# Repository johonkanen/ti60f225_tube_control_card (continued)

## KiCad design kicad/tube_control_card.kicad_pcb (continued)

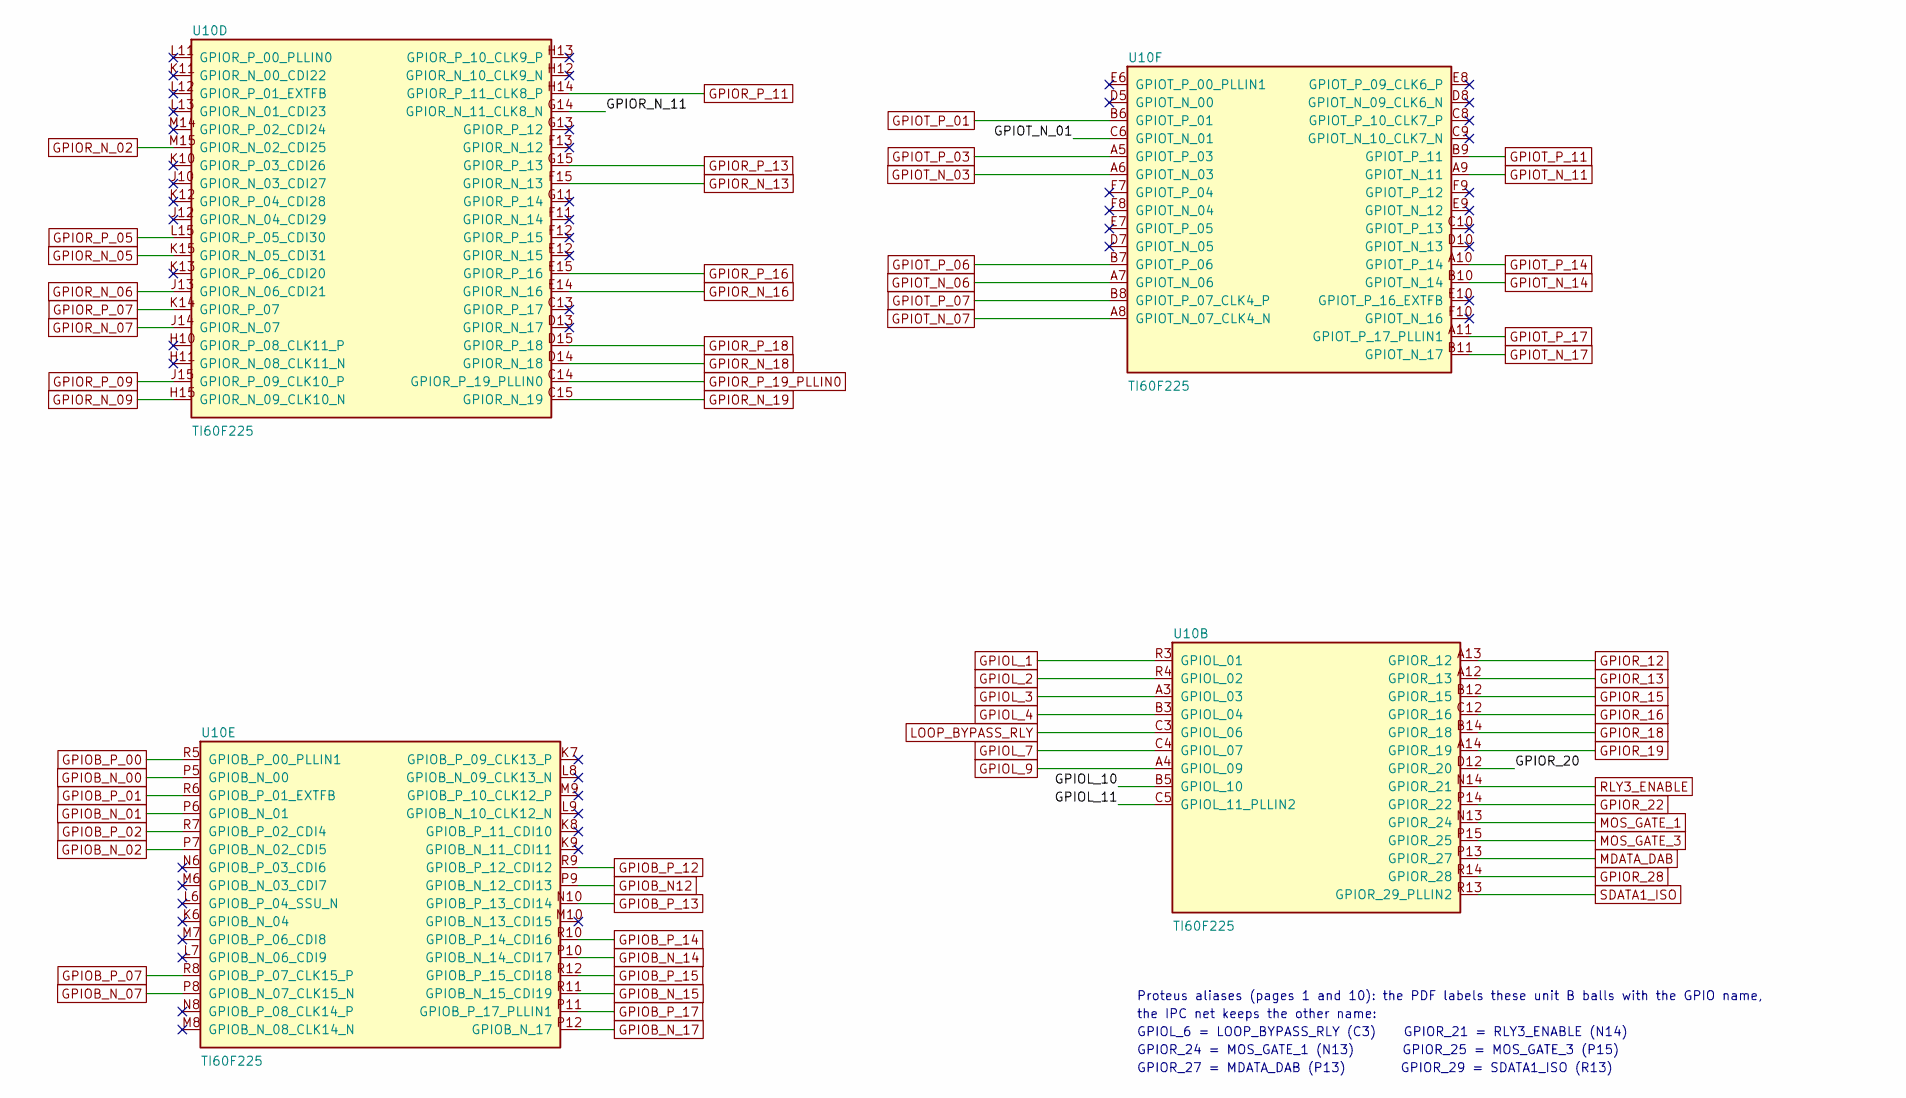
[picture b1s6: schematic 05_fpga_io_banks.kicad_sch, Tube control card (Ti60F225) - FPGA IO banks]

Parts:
U10: TI60F225; TFBGA-225_10x10mm_Layout15x15_P0.65mm

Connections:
/05 FPGA IO banks/GPIOL_10: U10.B5 (GPIOL_10); also elsewhere on the board
/05 FPGA IO banks/GPIOL_11: U10.C5 (GPIOL_11_PLLIN2); also elsewhere on the board
/05 FPGA IO banks/GPIOR_20: U10.D12 (GPIOR_20)
/05 FPGA IO banks/GPIOR_N_11: U10.G14 (GPIOR_N_11_CLK8_N)
/05 FPGA IO banks/GPIOT_N_01: U10.C6 (GPIOT_N_01)
GPIOB_N12: U10.P9 (GPIOB_N_12_CDI13); also elsewhere on the board
GPIOB_N_00: U10.P5 (GPIOB_N_00); also elsewhere on the board
GPIOB_N_01: U10.P6 (GPIOB_N_01); also elsewhere on the board
GPIOB_N_02: U10.P7 (GPIOB_N_02_CDI5); also elsewhere on the board
GPIOB_N_07: U10.P8 (GPIOB_N_07_CLK15_N); also elsewhere on the board
GPIOB_N_14: U10.P10 (GPIOB_N_14_CDI17); also elsewhere on the board
GPIOB_N_15: U10.R11 (GPIOB_N_15_CDI19); also elsewhere on the board
GPIOB_N_17: U10.P12 (GPIOB_N_17); also elsewhere on the board
GPIOB_P_00: U10.R5 (GPIOB_P_00_PLLIN1); also elsewhere on the board
GPIOB_P_01: U10.R6 (GPIOB_P_01_EXTFB); also elsewhere on the board
GPIOB_P_02: U10.R7 (GPIOB_P_02_CDI4); also elsewhere on the board
GPIOB_P_07: U10.R8 (GPIOB_P_07_CLK15_P); also elsewhere on the board
GPIOB_P_12: U10.R9 (GPIOB_P_12_CDI12); also elsewhere on the board
GPIOB_P_13: U10.N10 (GPIOB_P_13_CDI14); also elsewhere on the board
GPIOB_P_14: U10.R10 (GPIOB_P_14_CDI16); also elsewhere on the board
GPIOB_P_15: U10.R12 (GPIOB_P_15_CDI18); also elsewhere on the board
GPIOB_P_17: U10.P11 (GPIOB_P_17_PLLIN1); also elsewhere on the board
GPIOL_1: U10.R3 (GPIOL_01); also elsewhere on the board
GPIOL_2: U10.R4 (GPIOL_02); also elsewhere on the board
GPIOL_3: U10.A3 (GPIOL_03); also elsewhere on the board
GPIOL_4: U10.B3 (GPIOL_04); also elsewhere on the board
GPIOL_7: U10.C4 (GPIOL_07); also elsewhere on the board
GPIOL_9: U10.A4 (GPIOL_09); also elsewhere on the board
GPIOR_12: U10.A13 (GPIOR_12); also elsewhere on the board
GPIOR_13: U10.A12 (GPIOR_13); also elsewhere on the board
GPIOR_15: U10.B12 (GPIOR_15); also elsewhere on the board
GPIOR_16: U10.C12 (GPIOR_16); also elsewhere on the board
GPIOR_18: U10.B14 (GPIOR_18); also elsewhere on the board
GPIOR_19: U10.A14 (GPIOR_19); also elsewhere on the board
GPIOR_22: U10.P14 (GPIOR_22); also elsewhere on the board
GPIOR_28: U10.R14 (GPIOR_28); also elsewhere on the board
GPIOR_N_02: U10.M15 (GPIOR_N_02_CDI25); also elsewhere on the board
GPIOR_N_05: U10.K15 (GPIOR_N_05_CDI31); also elsewhere on the board
GPIOR_N_06: U10.J13 (GPIOR_N_06_CDI21); also elsewhere on the board
GPIOR_N_07: U10.J14 (GPIOR_N_07); also elsewhere on the board
GPIOR_N_09: U10.H15 (GPIOR_N_09_CLK10_N); also elsewhere on the board
GPIOR_N_13: U10.F15 (GPIOR_N_13); also elsewhere on the board
GPIOR_N_16: U10.E14 (GPIOR_N_16); also elsewhere on the board
GPIOR_N_18: U10.D14 (GPIOR_N_18); also elsewhere on the board
GPIOR_N_19: U10.C15 (GPIOR_N_19); also elsewhere on the board
GPIOR_P_05: U10.L15 (GPIOR_P_05_CDI30); also elsewhere on the board
GPIOR_P_07: U10.K14 (GPIOR_P_07); also elsewhere on the board
GPIOR_P_09: U10.J15 (GPIOR_P_09_CLK10_P); also elsewhere on the board
GPIOR_P_11: U10.H14 (GPIOR_P_11_CLK8_P); also elsewhere on the board
GPIOR_P_13: U10.G15 (GPIOR_P_13); also elsewhere on the board
GPIOR_P_16: U10.E15 (GPIOR_P_16); also elsewhere on the board
GPIOR_P_18: U10.D15 (GPIOR_P_18); also elsewhere on the board
GPIOR_P_19_PLLIN0: U10.C14 (GPIOR_P_19_PLLIN0); also elsewhere on the board
GPIOT_N_03: U10.A6 (GPIOT_N_03); also elsewhere on the board
GPIOT_N_06: U10.A7 (GPIOT_N_06); also elsewhere on the board
GPIOT_N_07: U10.A8 (GPIOT_N_07_CLK4_N); also elsewhere on the board
GPIOT_N_11: U10.A9 (GPIOT_N_11); also elsewhere on the board
GPIOT_N_14: U10.B10 (GPIOT_N_14); also elsewhere on the board
GPIOT_N_17: U10.B11 (GPIOT_N_17); also elsewhere on the board
GPIOT_P_01: U10.B6 (GPIOT_P_01); also elsewhere on the board
GPIOT_P_03: U10.A5 (GPIOT_P_03); also elsewhere on the board
GPIOT_P_06: U10.B7 (GPIOT_P_06); also elsewhere on the board
GPIOT_P_07: U10.B8 (GPIOT_P_07_CLK4_P); also elsewhere on the board
GPIOT_P_11: U10.B9 (GPIOT_P_11); also elsewhere on the board
GPIOT_P_14: U10.A10 (GPIOT_P_14); also elsewhere on the board
GPIOT_P_17: U10.A11 (GPIOT_P_17_PLLIN1); also elsewhere on the board
LOOP_BYPASS_RLY: U10.C3 (GPIOL_06); also elsewhere on the board
MDATA_DAB: U10.P13 (GPIOR_27); also elsewhere on the board
MOS_GATE_1: U10.N13 (GPIOR_24); also elsewhere on the board
MOS_GATE_3: U10.P15 (GPIOR_25); also elsewhere on the board
RLY3_ENABLE: U10.N14 (GPIOR_21); also elsewhere on the board
SDATA1_ISO: U10.R13 (GPIOR_29_PLLIN2); also elsewhere on the board

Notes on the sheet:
Proteus aliases (pages 1 and 10): the PDF labels these unit B balls with the GPIO name,
the IPC net keeps the other name:
GPIOL_6 = LOOP_BYPASS_RLY (C3) GPIOR_21 = RLY3_ENABLE (N14)
GPIOR_24 = MOS_GATE_1 (N13) GPIOR_25 = MOS_GATE_3 (P15)
GPIOR_27 = MDATA_DAB (P13) GPIOR_29 = SDATA1_ISO (R13)

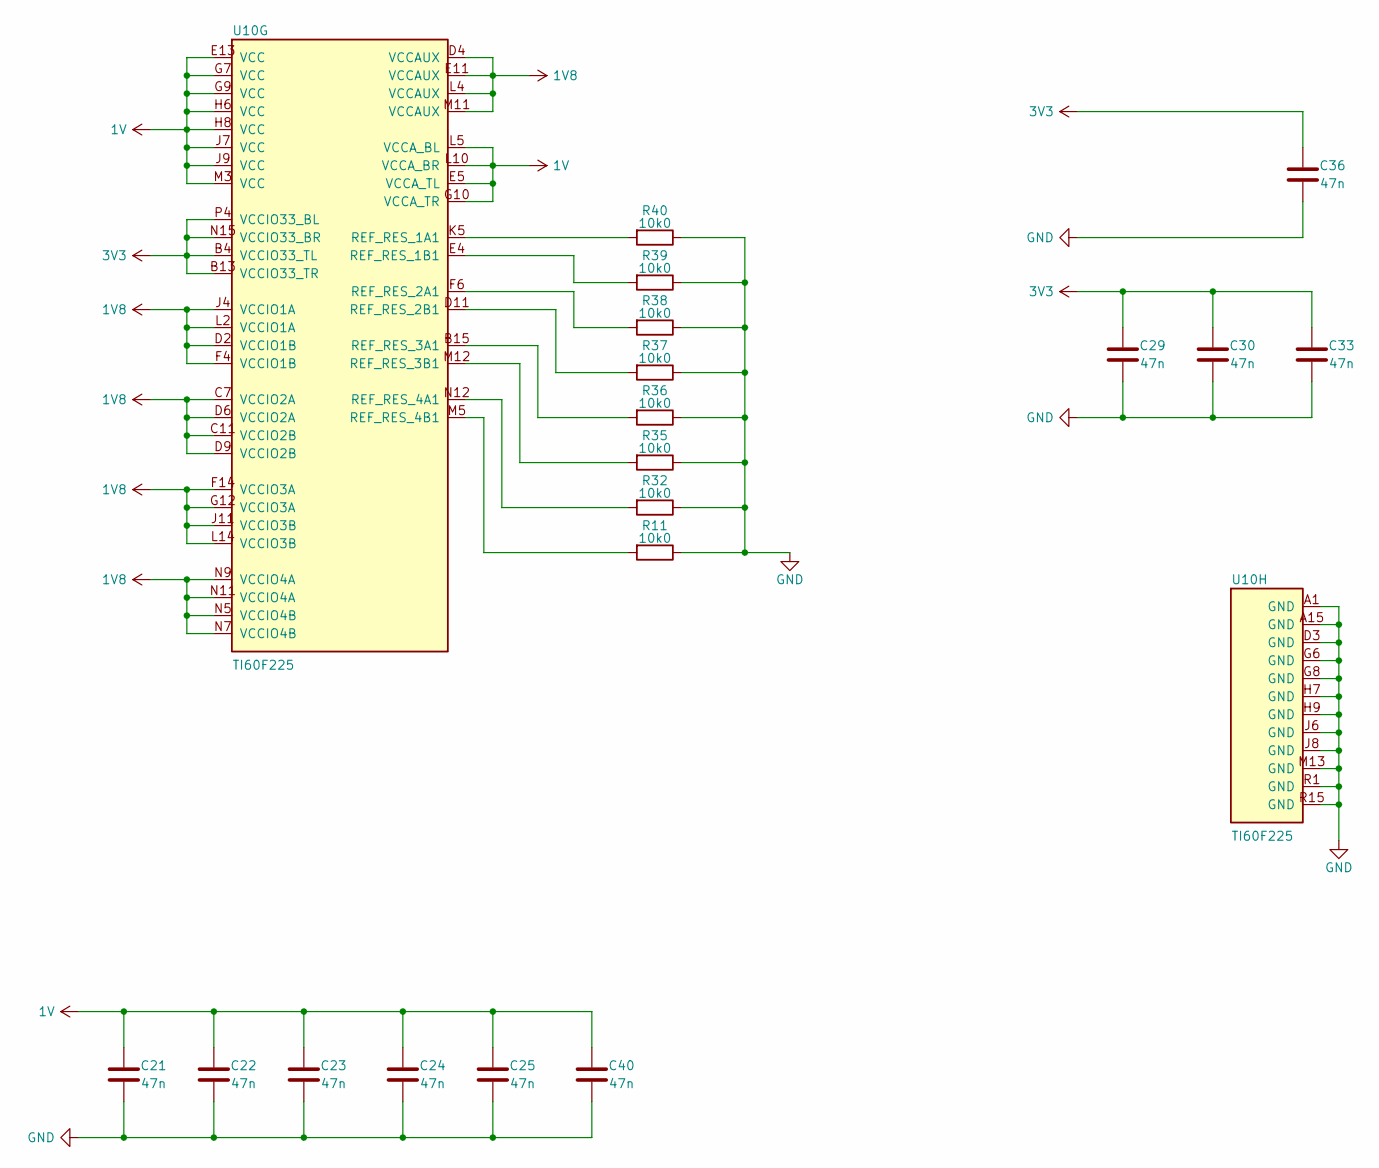
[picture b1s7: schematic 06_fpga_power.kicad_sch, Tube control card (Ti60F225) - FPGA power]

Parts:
C21, C22, C23, C24, C25, C29, C30, C33, C36, C40: 47n; C_0201_0603Metric
R11, R32, R35, R36, R37, R38, R39, R40: 10k0; R_0201_0603Metric
U10: TI60F225; TFBGA-225_10x10mm_Layout15x15_P0.65mm

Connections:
1V: C21.1, C22.1, C23.1, C24.1, C25.1, C40.1, U10.E5 (VCCA_TL), U10.E13 (VCC), U10.G7 (VCC), U10.G9 (VCC), U10.G10 (VCCA_TR), U10.H6 (VCC), U10.H8 (VCC), U10.J7 (VCC), U10.J9 (VCC), U10.L5 (VCCA_BL), U10.L10 (VCCA_BR), U10.M3 (VCC); also elsewhere on the board
1V8: U10.C7 (VCCIO2A), U10.C11 (VCCIO2B), U10.D2 (VCCIO1B), U10.D4 (VCCAUX), U10.D6 (VCCIO2A), U10.D9 (VCCIO2B), U10.E11 (VCCAUX), U10.F4 (VCCIO1B), U10.F14 (VCCIO3A), U10.G12 (VCCIO3A), U10.J4 (VCCIO1A), U10.J11 (VCCIO3B), U10.L2 (VCCIO1A), U10.L4 (VCCAUX), U10.L14 (VCCIO3B), U10.M11 (VCCAUX), U10.N5 (VCCIO4B), U10.N7 (VCCIO4B), U10.N9 (VCCIO4A), U10.N11 (VCCIO4A); also elsewhere on the board
3V3: C29.1, C30.1, C33.1, C36.1, U10.B4 (VCCIO33_TL), U10.B13 (VCCIO33_TR), U10.N15 (VCCIO33_BR), U10.P4 (VCCIO33_BL); also elsewhere on the board
GND: C21.2, C22.2, C23.2, C24.2, C25.2, C29.2, C30.2, C33.2, C36.2, C40.2, R11.1, R32.1, R35.1, R36.1, R37.1, R38.1, R39.1, R40.1, U10.A1 (GND), U10.A15 (GND), U10.D3 (GND), U10.G6 (GND), U10.G8 (GND), U10.H7 (GND), U10.H9 (GND), U10.J6 (GND), U10.J8 (GND), U10.M13 (GND), U10.R1 (GND), U10.R15 (GND); also elsewhere on the board
unnamed: R40.2, U10.K5 (REF_RES_1A1)
unnamed: R39.2, U10.E4 (REF_RES_1B1)
unnamed: R38.2, U10.F6 (REF_RES_2A1)
unnamed: R37.2, U10.D11 (REF_RES_2B1)
unnamed: R36.2, U10.B15 (REF_RES_3A1)
unnamed: R35.2, U10.M12 (REF_RES_3B1)
unnamed: R32.2, U10.N12 (REF_RES_4A1)
unnamed: R11.2, U10.M5 (REF_RES_4B1)

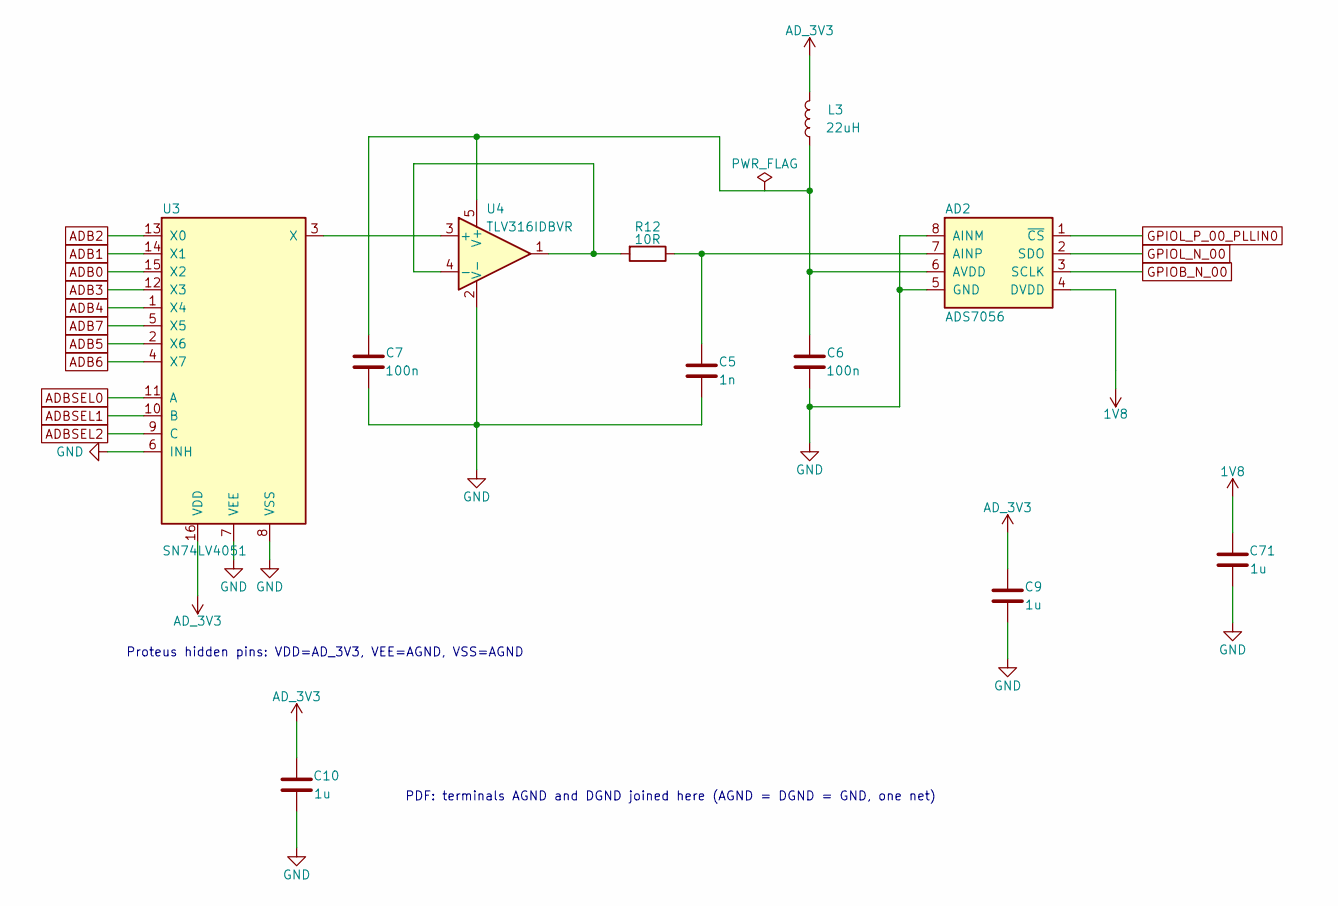
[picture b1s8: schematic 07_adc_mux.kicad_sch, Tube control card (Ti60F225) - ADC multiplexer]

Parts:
AD2: ADS7056; Texas_X2QFN-8_RUG_1.5x1.5mm_P0.5mm
C5: 1n; C_0402_1005Metric
C6, C7: 100n; C_0402_1005Metric
C9, C10, C71: 1u; C_0402_1005Metric
L3: 22uH; L_0805_2012Metric
R12: 10R; R_0402_1005Metric
U3: SN74LV4051; TSSOP-16_4.4x5mm_P0.65mm_ProteusPads
U4: TLV316IDBVR; SOT-23-5_Proteus_ProteusPads

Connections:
1V8: AD2.4 (DVDD), C71.2; also elsewhere on the board
ADB0: U3.15 (X2); also elsewhere on the board
ADB1: U3.14 (X1); also elsewhere on the board
ADB2: U3.13 (X0); also elsewhere on the board
ADB3: U3.12 (X3); also elsewhere on the board
ADB4: U3.1 (X4); also elsewhere on the board
ADB5: U3.2 (X6); also elsewhere on the board
ADB6: U3.4 (X7); also elsewhere on the board
ADB7: U3.5 (X5); also elsewhere on the board
ADBSEL0: U3.11 (A); also elsewhere on the board
ADBSEL1: U3.10 (B); also elsewhere on the board
ADBSEL2: U3.9 (C); also elsewhere on the board
AD_3V3: C9.2, C10.2, L3.2, U3.16 (VDD); also elsewhere on the board
GND: AD2.5 (GND), AD2.8 (AINM), C5.1, C6.1, C7.1, C9.1, C10.1, C71.1, U3.6 (INH), U3.7 (VEE), U3.8 (VSS), U4.2 (V-); also elsewhere on the board
GPIOB_N_00: AD2.3 (SCLK); also elsewhere on the board
GPIOL_N_00: AD2.2 (SDO); also elsewhere on the board
GPIOL_P_00_PLLIN0: AD2.1 (~CS); also elsewhere on the board
unnamed: AD2.7 (AINP), C5.2, R12.1
unnamed: AD2.6 (AVDD), C6.2, C7.2, L3.1, U4.5 (V+)
unnamed: U3.3 (X), U4.3 (+)
unnamed: R12.2, U4.1, U4.4 (-)

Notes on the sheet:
Proteus hidden pins: VDD=AD_3V3, VEE=AGND, VSS=AGND
PDF: terminals AGND and DGND joined here (AGND = DGND = GND, one net)

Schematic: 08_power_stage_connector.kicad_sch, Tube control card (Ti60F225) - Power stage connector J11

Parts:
C53, C54: 100n; C_0603_1608Metric
J11: 40 PIN HEADER 50TH; PinHeader_2x20_P1.27mm_Vertical_ProteusPads

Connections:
3V3: C54.1, J11.35, J11.36; also elsewhere on the board
12V: C53.1, J11.39, J11.40; also elsewhere on the board
ADASEL0_ISO: J11.11; also elsewhere on the board
ADASEL1_ISO: J11.10; also elsewhere on the board
ADASEL2_ISO: J11.9; also elsewhere on the board
ADB0: J11.2; also elsewhere on the board
ADB1: J11.4; also elsewhere on the board
ADB2: J11.6; also elsewhere on the board
ADB3: J11.8; also elsewhere on the board
ADB4: J11.7; also elsewhere on the board
ADB5: J11.5; also elsewhere on the board
ADB6: J11.3; also elsewhere on the board
ADB7: J11.1; also elsewhere on the board
ADCLK_DAB: J11.24; also elsewhere on the board
CLK1_ISO: J11.14; also elsewhere on the board
CS1_ISO: J11.13; also elsewhere on the board
DAB_PWM_HI_SEC: J11.27; also elsewhere on the board
DAB_PWM_LO_SEC: J11.29; also elsewhere on the board
DAB_PWM_PRI_HI_ISO: J11.22; also elsewhere on the board
DAB_PWM_PRI_LO_ISO: J11.23; also elsewhere on the board
GND: C53.2, C54.2, J11.33, J11.34; also elsewhere on the board
INU_ADCLK: J11.32; also elsewhere on the board
MDATA_DAB: J11.26; also elsewhere on the board
PWM_G1_ISO: J11.20; also elsewhere on the board
PWM_G2_ISO: J11.19; also elsewhere on the board
PWM_G3_ISO: J11.21; also elsewhere on the board
PWM_G4_ISO: J11.18; also elsewhere on the board
PWM_Q5: J11.30; also elsewhere on the board
PWM_Q6: J11.31; also elsewhere on the board
PWM_TRANS1_ISO: J11.15; also elsewhere on the board
PWM_TRANS2_ISO: J11.16; also elsewhere on the board
PWM_TRANS3_ISO: J11.17; also elsewhere on the board
PWM_TRANS4: J11.25; also elsewhere on the board
PWM_TRANS6: J11.28; also elsewhere on the board
SDATA1_ISO: J11.12; also elsewhere on the board

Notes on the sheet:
Unconnected terminals in the PDF (no net):
T_IRQ, T_DO, T_DIN, T_CS, T_CK, MOSI, LED, SCK, MISO, DATA/COMMAND, LCD_RESET, LCD_CS, ISOGND, 3V3
Unconnected terminals in the PDF (no net): ADB2, ADB1, ADB0, ADB3, ADB4, AGND, ADB5, ADB6
PDF DGND = GND (one net with AGND, gnd, ISOGND).

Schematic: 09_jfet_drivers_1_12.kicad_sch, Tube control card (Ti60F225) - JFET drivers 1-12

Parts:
R14, R22, R24: 10k; R_Array_Convex_4x0402_Proteus
R15, R23, R25: 47k; R_Array_Convex_4x0402_Proteus
U5, U6, U11: TLV9304PWR; TSSOP-14_4.4x5mm_P0.65mm_Proteus_ProteusPads

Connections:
3V3: U5.4 (V+), U6.4 (V+), U11.4 (V+); also elsewhere on the board
/09 JFET drivers 1-12/JFET_3: R15.1 (R1.1), U5.1
/09 JFET drivers 1-12/JFET_4: R15.2 (R2.1), U5.7
/09 JFET drivers 1-12/JFET_5: R23.4 (R4.1), U6.14; also elsewhere on the board
/09 JFET drivers 1-12/JFET_6: R23.3 (R3.1), U6.8; also elsewhere on the board
A: R15.3 (R3.1), U5.8; also elsewhere on the board
GND: U5.3 (+), U5.5 (+), U5.10 (+), U5.12 (+), U6.3 (+), U6.5 (+), U6.10 (+), U6.12 (+), U11.3 (+), U11.5 (+), U11.10 (+), U11.12 (+); also elsewhere on the board
GPIOL_N_14: R14.6 (R3.2); also elsewhere on the board
GPIOL_P_14: R14.5 (R4.2); also elsewhere on the board
GPIOL_P_15: R14.7 (R2.2); also elsewhere on the board
GPIOR_12: R24.7 (R2.2); also elsewhere on the board
GPIOR_13: R24.5 (R4.2); also elsewhere on the board
GPIOR_15: R24.6 (R3.2); also elsewhere on the board
GPIOR_19: R24.8 (R1.2); also elsewhere on the board
GPIOT_N_14: R22.6 (R3.2); also elsewhere on the board
GPIOT_N_17: R22.8 (R1.2); also elsewhere on the board
GPIOT_P_03: R14.8 (R1.2); also elsewhere on the board
GPIOT_P_14: R22.5 (R4.2); also elsewhere on the board
GPIOT_P_17: R22.7 (R2.2); also elsewhere on the board
JFET_2: R15.4 (R4.1), U5.14; also elsewhere on the board
JFET_7: R23.1 (R1.1), U6.1; also elsewhere on the board
JFET_8: R23.2 (R2.1), U6.7; also elsewhere on the board
JFET_9: R25.3 (R3.1), U11.8; also elsewhere on the board
JFET_10: R25.4 (R4.1), U11.14; also elsewhere on the board
JFET_11: R25.1 (R1.1), U11.1; also elsewhere on the board
JFET_12: R25.2 (R2.1), U11.7; also elsewhere on the board
unnamed: R14.1 (R1.1), R15.8 (R1.2), U5.2 (-)
unnamed: R14.2 (R2.1), R15.7 (R2.2), U5.6 (-)
unnamed: R14.3 (R3.1), R15.6 (R3.2), U5.9 (-)
unnamed: R14.4 (R4.1), R15.5 (R4.2), U5.13 (-)
unnamed: R22.1 (R1.1), R23.8 (R1.2), U6.2 (-)
unnamed: R22.2 (R2.1), R23.7 (R2.2), U6.6 (-)
unnamed: R22.3 (R3.1), R23.6 (R3.2), U6.9 (-)
unnamed: R22.4 (R4.1), R23.5 (R4.2), U6.13 (-)
unnamed: R24.1 (R1.1), R25.8 (R1.2), U11.2 (-)
unnamed: R24.2 (R2.1), R25.7 (R2.2), U11.6 (-)
unnamed: R24.3 (R3.1), R25.6 (R3.2), U11.9 (-)
unnamed: R24.4 (R4.1), R25.5 (R4.2), U11.13 (-)
OPAMP_-15V: U5.11 (V-), U6.11 (V-), U11.11 (V-); also elsewhere on the board

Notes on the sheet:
Proteus alias pairs of this page (the IPC name, left, is used on the pins):
GPIOR_19 = JFET_GPIO_11
GPIOR_12 = JFET_GPIO_12
GPIOR_15 = JFET_GPIO_9
GPIOR_13 = JFET_GPIO_10
GPIOT_N_17 = JFET_GPIO_7
GPIOT_P_17 = JFET_GPIO_8
GPIOT_N_14 = JFET_GPIO_6
GPIOT_P_14 = JFET_GPIO_5
GPIOL_10 = JFET_GPIO_3
GPIOT_P_03 = JFET_GPIO_4
GPIOL_11 = JFET_GPIO_1
GPIOL_9 = JFET_GPIO_2
U5:C output: PDF JFET_1 = IPC net A (alias pair of page 10)
PDF: a terminal JFET_GPIO_1 (= GPIOL_11) with an open wire stub stands above U5:C: no connection.
JFET_GPIO_1, _2, _3 (GPIOL_11, GPIOL_9, GPIOL_10) feed no driver on this page: the cells of JFET_1, JFET_2
and JFET_4 take GPIOL_N_14, GPIOL_P_14 and GPIOL_P_15 (STATUS.md findings).
JFET_3 and JFET_4 reach no other part; JFET_5 and JFET_6 only an SMD test pad each (STATUS.md findings).

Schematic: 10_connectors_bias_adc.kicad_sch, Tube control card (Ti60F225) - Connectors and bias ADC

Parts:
ADC1: ADC121C027; SOT-23-6_ADC121C027_Proteus_ProteusPads
C67: 100n; C_0402_1005Metric
C68: 1n; C_0402_1005Metric
J3, J6: 16 PIN HEADER 50TH; PinHeader_2x08_P1.27mm_Vertical
J7: 30 PIN HEADER 50TH; PinHeader_2x15_P1.27mm_Vertical_ProteusPads
R31, R33: 2k; R_0402_1005Metric
R34: 100; R_0402_1005Metric

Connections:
3V3: ADC1.A1 (VA), C67.2, J6.1, J6.2, J7.29, J7.30, R31.1, R33.1; also elsewhere on the board
/10 Connectors and bias ADC/BIASFEEDBACK: J6.5, R34.1
A: J3.1; also elsewhere on the board
BIASREF: J6.15, J6.16; also elsewhere on the board
GND: ADC1.A2 (GND), C67.1, C68.1, J3.2, J3.4, J3.6, J3.8, J3.10, J3.12, J3.14, J3.16, J6.3, J6.4, J7.27, J7.28; also elsewhere on the board
GPIOL_P_16: J6.7; also elsewhere on the board
GPIOL_P_17: J3.13; also elsewhere on the board
GPIOR_22: ADC1.K1 (SCL), R33.2; also elsewhere on the board
GPIOR_28: ADC1.COM1 (SDA), R31.2; also elsewhere on the board
GPIOT_N_03: J7.2; also elsewhere on the board
GPIOT_N_06: J7.3; also elsewhere on the board
GPIOT_N_07: J7.5; also elsewhere on the board
GPIOT_N_11: J7.7; also elsewhere on the board
GPIOT_P_01: J7.1; also elsewhere on the board
GPIOT_P_06: J7.4; also elsewhere on the board
GPIOT_P_07: J7.6; also elsewhere on the board
GPIOT_P_11: J7.8; also elsewhere on the board
JFET_2: J3.3; also elsewhere on the board
JFET_7: J7.10; also elsewhere on the board
JFET_8: J7.9; also elsewhere on the board
JFET_9: J7.12; also elsewhere on the board
JFET_10: J7.11; also elsewhere on the board
JFET_11: J7.14; also elsewhere on the board
JFET_12: J7.13; also elsewhere on the board
JFET_13: J3.7; also elsewhere on the board
JFET_14: J3.5; also elsewhere on the board
JFET_15: J3.9; also elsewhere on the board
JFET_16: J3.11; also elsewhere on the board
LOOP_BYPASS_RLY: J3.15; also elsewhere on the board
MOS_GATE_1: J7.25; also elsewhere on the board
MOS_GATE_2: J7.19; also elsewhere on the board
MOS_GATE_3: J7.18; also elsewhere on the board
MOS_GATE_4: J7.26; also elsewhere on the board
MOS_GATE_5: J7.24; also elsewhere on the board
unnamed: ADC1.COM2 (VIN), C68.2, R34.2
POWERSCL: J6.11; also elsewhere on the board
POWERSDA: J6.9; also elsewhere on the board
RLY1_ENABLE: J7.23; also elsewhere on the board
RLY2_ENABLE: J7.22; also elsewhere on the board
RLY3_ENABLE: J7.20; also elsewhere on the board
RLY4_ENABLE: J7.21; also elsewhere on the board
RLY5_ENABLE: J7.17; also elsewhere on the board
RLY6_ENABLE: J7.15; also elsewhere on the board
RLY7_ENABLE: J7.16; also elsewhere on the board

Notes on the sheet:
Proteus alias pairs of this page (the IPC name is used on the pins):
GPIOL_6 = LOOP_BYPASS_RLY (IPC LOOP_BYPASS_RLY, J3 pin 15)
JFET_1 = A (IPC A, J3 pin 1)
JFET_13 = C' (IPC JFET_13, J3 pin 7)
JFET_15 = D' (IPC JFET_15, J3 pin 9)
POWERSDA = GPIOL_N_17 (IPC POWERSDA, J6 pin 9)
POWERSCL = GPIOL_N_16 (IPC POWERSCL, J6 pin 11)
Unconnected terminals in the PDF (no net): JFET_GATE_x3, _x1, _10, _8, _5, _9, _x2, _3, _2, _6, _7, _4
ADC1: Proteus pin ids A1 = VA, A2 = GND, COM1 = SDA, COM2 = VIN, K1 = SCL, K2 = ADR0;
Hand edit 2026-11-20 (finding 9): VA on 3V3, VIN on the filtered input (the PDF has them swapped).

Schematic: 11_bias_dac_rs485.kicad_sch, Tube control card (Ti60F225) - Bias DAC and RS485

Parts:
C4: 200p; C_0402_1005Metric
C51: 100n; C_0603_1608Metric
C55, C58: 10u; C_1206_3216Metric
ISO5V: TERMINAL; Terminal_2x1_P5.00mm_D2.0mm_Drill1.4mm
ISO_G: TERMINAL; Terminal_2x1_P5.00mm_D2.0mm_Drill1.4mm
PWR4: IZB03; Converter_IZB03_SIP7
R19, R26, R59: 2k; R_0402_1005Metric
R67, R68, R69: 100k; R_1206_3216Metric_Pad1.30x1.75mm_HandSolder
RS1: MAX22025; SOIC-8_7.5x5.85mm_P1.27mm_Proteus
RS485A, RS485B: TERMINAL; Terminal_2x1_P5.00mm_D2.0mm_Drill1.4mm
U12: AD5622; SOT-363_SC-70-6_Proteus_ProteusPads

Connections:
1V8: C51.1, RS1.3 (VDDA); also elsewhere on the board
3V3: R19.2, R26.2, U12.4 (VA); also elsewhere on the board
5V: C55.2, PWR4.2 (Vin+); also elsewhere on the board
BIASREF: C4.2, R59.2, U12.6 (VOUT); also elsewhere on the board
GND: C4.1, C51.2, C55.1, PWR4.1 (Vin-), R59.1, RS1.4 (GNDA), U12.1 (ADDR), U12.5 (GND); also elsewhere on the board
GPIOR_16: R26.1, U12.3 (SCA); also elsewhere on the board
GPIOR_18: R19.1, U12.2 (SCL); also elsewhere on the board
ISO5V: C58.1, ISO5V.1, PWR4.5 (Vout+), R68.1, RS1.8 (VDDB)
unnamed: R67.2, R69.1, RS1.6 (A), RS485A.1
unnamed: R67.1, R68.2, RS1.7 (B), RS485B.1
RS485_GND: C58.2, ISO_G.1, PWR4.6 (Vout-), R69.2, RS1.5 (GNDB)
RXD: RS1.1 (RXD); also elsewhere on the board
TXD: RS1.2 (TXD); also elsewhere on the board

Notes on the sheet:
I2C address = 11
3-state io
use reference
Proteus alias: bias_feedback = biasref (terminal on the BIASREF node; the page 10 name is biasfeedback)
Proteus alias: GPIOR_18 = dac_clock
Proteus alias: GPIOR_16 = dac_data
VDDA either 3v3 or 1v8
VDDB max 5.25v
Terminals ISO5V, ISO_G, RS485A, RS485B: one pin each, two pads on the board (decision D1, STATUS.md).

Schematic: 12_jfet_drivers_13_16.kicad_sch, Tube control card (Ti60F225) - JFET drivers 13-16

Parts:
C59, C60, C61, C62, C63, C64, C65, C66: 100n; C_0402_1005Metric
R17: 10k; R_Array_Convex_4x0402_Proteus
R18: 47k; R_Array_Convex_4x0402_Proteus
U14: TL084HIDYYR; TSSOP-14_4.4x5mm_P0.65mm_Proteus_ProteusPads

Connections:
3V3: C60.2, C62.2, C64.2, C66.2, U14.4 (V+); also elsewhere on the board
GND: C59.2, C60.1, C61.2, C62.1, C63.2, C64.1, C65.2, C66.1, U14.3 (+), U14.5 (+), U14.10 (+), U14.12 (+); also elsewhere on the board
GPIOL_3: R17.7 (R2.2); also elsewhere on the board
GPIOL_4: R17.6 (R3.2); also elsewhere on the board
GPIOL_7: R17.5 (R4.2); also elsewhere on the board
GPIOL_9: R17.8 (R1.2); also elsewhere on the board
JFET_13: R18.2 (R2.1), U14.7; also elsewhere on the board
JFET_14: R18.1 (R1.1), U14.1; also elsewhere on the board
JFET_15: R18.3 (R3.1), U14.8; also elsewhere on the board
JFET_16: R18.4 (R4.1), U14.14; also elsewhere on the board
unnamed: R17.1 (R1.1), R18.8 (R1.2), U14.2 (-)
unnamed: R17.2 (R2.1), R18.7 (R2.2), U14.6 (-)
unnamed: R17.3 (R3.1), R18.6 (R3.2), U14.9 (-)
unnamed: R17.4 (R4.1), R18.5 (R4.2), U14.13 (-)
OPAMP_-15V: C59.1, C61.1, C63.1, C65.1, U14.11 (V-); also elsewhere on the board

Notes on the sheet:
PDF page 9 alias: GPIOL_9 = JFET_GPIO_2 (the input of the JFET_14 driver)

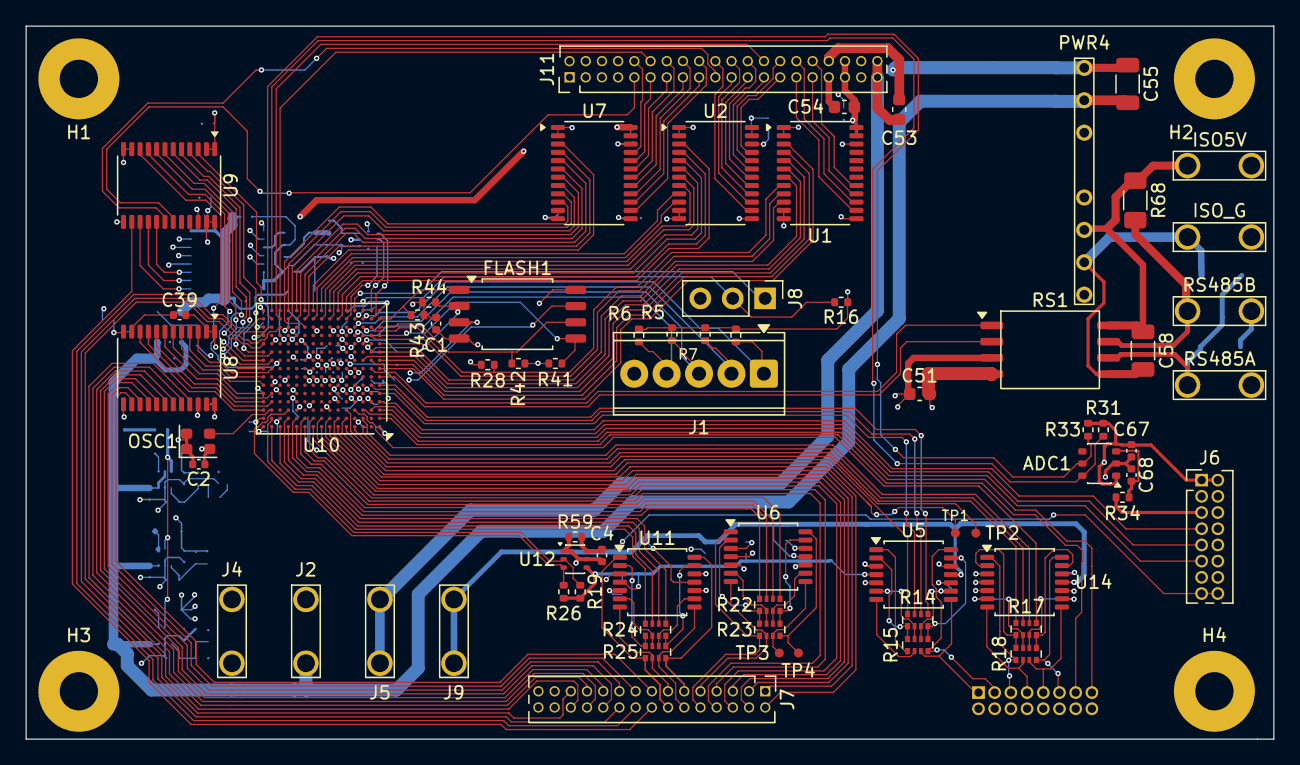
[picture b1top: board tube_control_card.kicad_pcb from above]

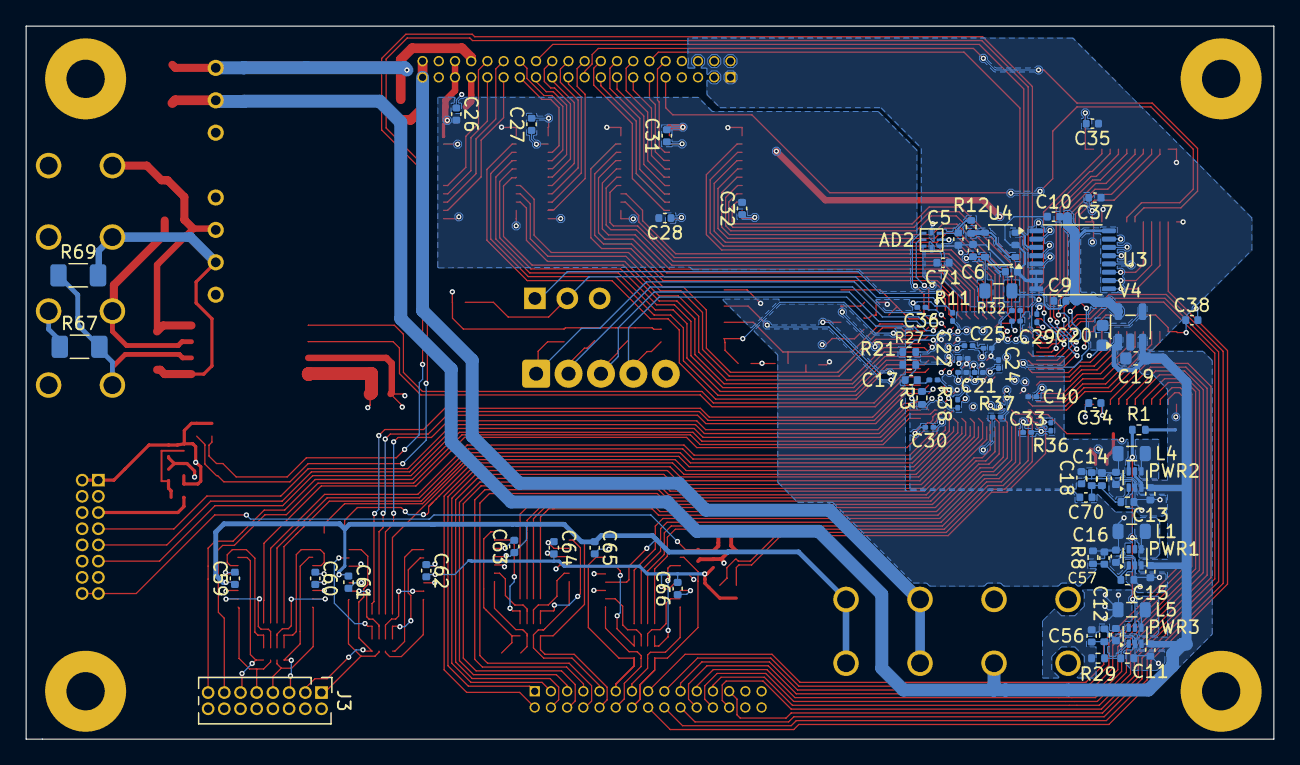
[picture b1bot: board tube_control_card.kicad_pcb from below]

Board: 4 copper layers, 97.8 x 55.9 mm, 154 parts (81 on the bottom side), 210 nets.

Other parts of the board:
H1, H2, H3, H4: MountingHole_3.0mm_PTH; MountingHole_3.0mm_PTH_Pad6.35mm
TP1, TP2, TP3, TP4: TestPad; TestPad_SMD_D0.711mm

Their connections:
/05 FPGA IO banks/GPIOL_10: TP1.1; also elsewhere on the board
/05 FPGA IO banks/GPIOL_11: TP2.1; also elsewhere on the board
/09 JFET drivers 1-12/JFET_5: TP4.1; also elsewhere on the board
/09 JFET drivers 1-12/JFET_6: TP3.1; also elsewhere on the board
